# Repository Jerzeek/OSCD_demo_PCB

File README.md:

# OSCD Demo PCB

A demonstration / teaching PCB built by the [Open Science Community Delft](https://www.tudelft.nl/en/library/open-science-community-delft) to show what an open hardware project looks like in practice: full sources, an open licence, and everything needed to have the board made and reprogrammed by anyone.

It is a round, ~93 mm ESP32-C3 board shaped like the OSCD logo, with a ring of 12 addressable RGB LEDs, three sensors on a shared I²C bus, capacitive touch pads, and three push buttons. Plug it into USB-C, and the demo firmware lights the ring in response to tilt, touch, ambient light, and button presses.

| | |
|---|---|
| **Revision** | 1.0 |
| **Designer** | Dr. ir. Tim M. J. Nijssen, Open Science Community Delft |
| **Licence** | [CERN-OHL-P v2](LICENSE) (permissive) |
| **EDA tool** | KiCad (2026-era release — see [Opening the design](#opening-the-design)) |

---

## Features

| Block | Part | Interface |
|---|---|---|
| Microcontroller | ESP32-C3-MINI-1 (RISC-V, Wi-Fi + BLE, native USB) | — |
| RGB LEDs | 12 × WS2812B-2020, in a 63 mm ring | 1-wire, `GPIO8` |
| IMU | LSM6DS3 — 3-axis accelerometer + gyroscope | I²C `0x6A` |
| Ambient light | APDS-9306-065 | I²C `0x52` |
| Capacitive touch | MPR121 — 12 electrodes (6 buttons + 6-pad slider) | I²C `0x5A`, IRQ on `GPIO10` |
| Buttons | 3 × user push button, plus RESET and BOOT | `GPIO0/1/2` |
| Power | USB-C 5 V → HT7533-1 LDO → 3.3 V | — |
| Breakout | 2 × 2×5 pin header (5 V, 3.3 V, GND, 9 GPIO) | 2.54 mm |
| Test points | 5 V, 3.3 V, SDA, SCL (each via 100 Ω) | — |

There is no USB-UART bridge — the ESP32-C3's native USB peripheral is wired straight to the USB-C connector, protected by a USBLC6-2SC6 ESD array.

## Quick start

1. **Power it.** Connect a USB-C cable to `J1`. The board is bus-powered; no battery or jumper setting is needed.
2. **Install the toolchain.** Arduino IDE with the *esp32* board package by Espressif, board **ESP32C3 Dev Module**, and **Tools → USB CDC On Boot: Enabled**.
3. **Flash the demo.** Open [`firmware_examples/test_sensors/test_sensors.ino`](firmware_examples/test_sensors/test_sensors.ino) and upload it. Because there is no auto-reset circuit you must enter the bootloader by hand: **hold BOOT (SW2), tap RESET (SW1), release BOOT**, then click Upload. Tap RESET again when the upload finishes.
4. **Watch it.** The ring plays a rainbow sweep at boot, then reacts to tilt, touch, and the three buttons. Open the Serial Monitor at 115200 baud for sensor readings.

Full setup notes, required libraries, and troubleshooting are in [`firmware_examples/README.md`](firmware_examples/README.md).

## Pinout

| ESP32-C3 pin | Function on this board | Also on |
|---|---|---|
| `GPIO0` | Button **SW4** (active low, RC-debounced) | `J2.6` |
| `GPIO1` | Button **SW3** (active low, RC-debounced) | `J2.7` |
| `GPIO2` | Button **SW5** (active low, RC-debounced) | `J2.3` |
| `GPIO3` | APDS-9306 interrupt | `J2.4` |
| `GPIO4` | LSM6DS3 `INT1` | `J2.9` |
| `GPIO5` | LSM6DS3 `INT2` | `J3.3` |
| `GPIO6` | **I²C SCL** (4.7 kΩ pull-up) | `J3.4`, `TP5` |
| `GPIO7` | **I²C SDA** (4.7 kΩ pull-up) | `J3.5`, `TP6` |
| `GPIO8` | WS2812B data out → `D1` | `J3.6` |
| `GPIO9` | BOOT button **SW2** (strapping pin) | `J3.7` |
| `GPIO10` | MPR121 `IRQ` | `J2.8` |
| `GPIO18/19` | USB D− / D+ | — |
| `GPIO20/21` | UART0 RX / TX | `J3.8`, `J3.9` |
| `EN` | RESET button **SW1** | `J2.5` |

**Header pinouts** (2×5, 2.54 mm, odd/even numbering):

```
J2:  1 +5V    2 +3V3    3 GPIO2   4 GPIO3   5 EN
     6 GPIO0  7 GPIO1   8 GPIO10  9 GPIO4  10 GND

J3:  1 +5V    2 +3V3    3 GPIO5   4 GPIO6   5 GPIO7
     6 GPIO8  7 GPIO9   8 GPIO20  9 GPIO21 10 GND
```

**LED ring order:** `D1` sits at the 9 o'clock position and the chain `D1 → D2 → … → D12` runs clockwise, 30° apart.

**Touch electrodes:** `TP2` is the inner 6-pad slider on `ELE0…ELE5`; `TP1` is the outer ring of 6 buttons on `ELE6…ELE11`.

## Repository layout

```
OSCD_demo_PCB.kicad_pro     KiCad project
OSCD_demo_PCB.kicad_sch     Schematic (single sheet)
OSCD_demo_PCB.kicad_pcb     Board layout (4 layers)
schematic.pdf               Rendered schematic, for reading without KiCad
assets/
  OSCD_demo_PCB_symbols.kicad_sym    Project-local symbols
  OSCD_demo_PCB_footprints.pretty/   Project-local footprints (ESP32 module,
                                     touch pads, WS2812B-2020, logo, switches)
  graphics/                          OSCD logo artwork (DXF)
bom/ibom.html               Interactive HTML BOM for hand assembly
production/                 Fabrication outputs (gerbers, drill, BOM, CPL)
firmware_examples/          Arduino sketches
docs/                       Hardware and manufacturing documentation
```

## Opening the design

The sources were saved by a 2026-era KiCad release (schematic file format `20260306`, board format `20260206`). Open them with that release or newer; older KiCad versions will refuse the files.

Symbol and footprint libraries are project-local and resolved through `${KIPRJMOD}` in `sym-lib-table` / `fp-lib-table`, so cloning the repository and opening `OSCD_demo_PCB.kicad_pro` is enough — nothing has to be installed into your global libraries.

## Documentation

- **[docs/hardware.md](docs/hardware.md)** — how each subsystem works, jumper/configuration options, and design notes.
- **[docs/manufacturing.md](docs/manufacturing.md)** — board specification, ordering, and how to regenerate the fabrication files.
- **[firmware_examples/README.md](firmware_examples/README.md)** — toolchain setup, upload procedure, and what the demo does.

## Licence

Hardware and firmware are released under the **CERN Open Hardware Licence Version 2 – Permissive** ([`LICENSE`](LICENSE)). You may use, study, modify, manufacture and sell boards based on this design, including in closed-source products, provided you keep the copyright and licence notices and do not imply endorsement.

The OSCD logo and name are project branding; please replace them with your own if you distribute modified boards.

## Credits

Designed by Dr. ir. Tim M. J. Nijssen for the Open Science Community Delft.

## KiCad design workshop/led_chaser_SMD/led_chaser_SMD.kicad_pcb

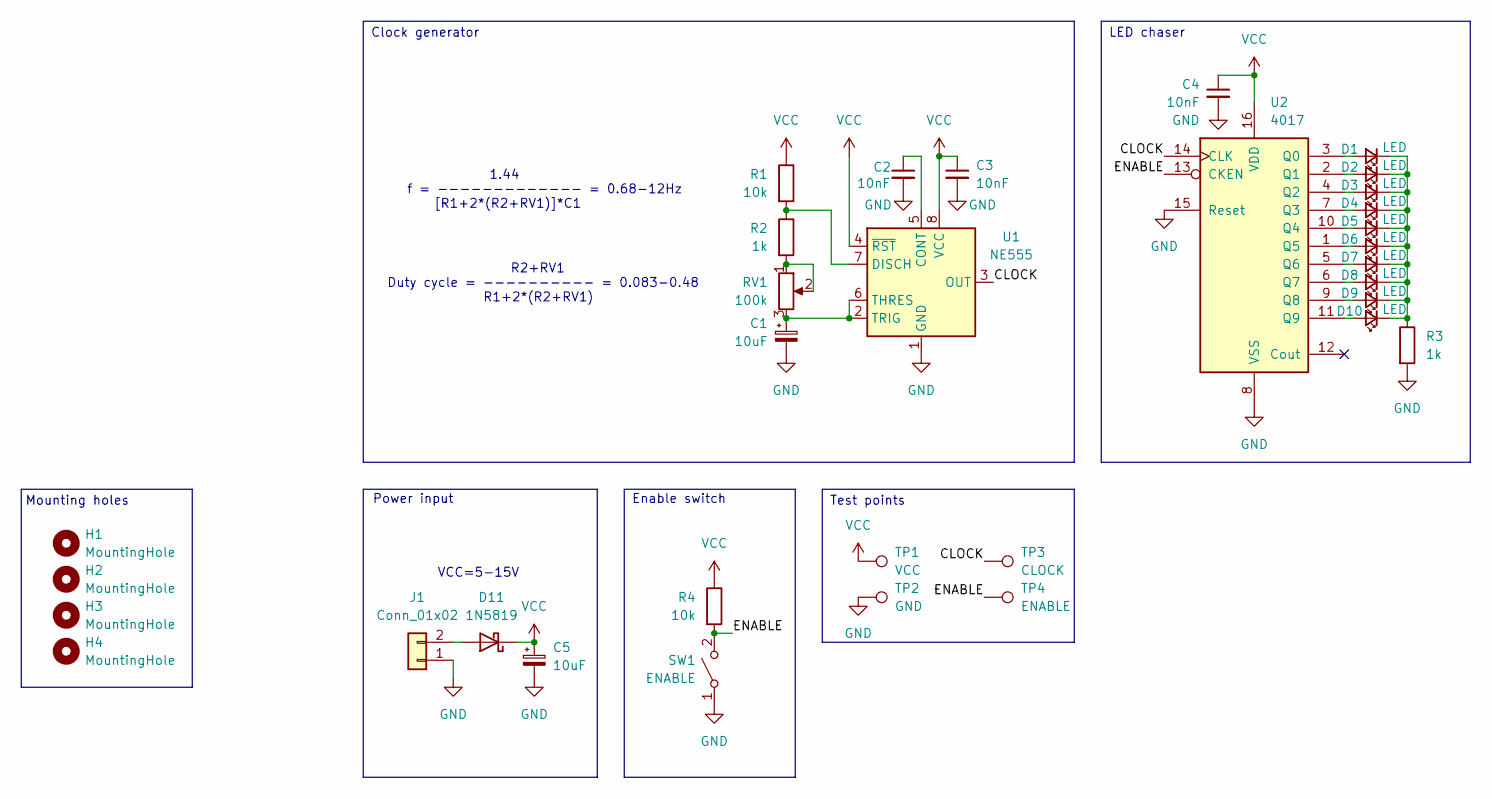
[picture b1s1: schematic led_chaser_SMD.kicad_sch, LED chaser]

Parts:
C1, C5: 10uF; C_0805_2012Metric_Pad1.18x1.45mm_HandSolder
C2, C3, C4: 10nF; C_0805_2012Metric_Pad1.18x1.45mm_HandSolder
D1, D2, D3, D4, D5, D6, D7, D8, D9, D10: LED; LED_0805_2012Metric_Pad1.15x1.40mm_HandSolder
D11: 1N5819; D_SOD-323
H1, H2, H3, H4: MountingHole; MountingHole_3.2mm_M3
J1: Conn_01x02; JST_XH_B2B-XH-A_1x02_P2.50mm_Vertical
R1, R4: 10k; R_0805_2012Metric_Pad1.20x1.40mm_HandSolder
R2, R3: 1k; R_0805_2012Metric_Pad1.20x1.40mm_HandSolder
RV1: 100k; Potentiometer_Bourns_TC33X_Vertical
SW1: ENABLE; SW_DIP_SPSTx01_Slide_6.7x4.1mm_W8.61mm_P2.54mm_LowProfile
TP1: VCC; TestPoint_Pad_D2.0mm
TP2: GND; TestPoint_Pad_D2.0mm
TP3: CLOCK; TestPoint_Pad_D2.0mm
TP4: ENABLE; TestPoint_Pad_D2.0mm
U1: NE555; SOIC-8_3.9x4.9mm_P1.27mm
U2: 4017; SOIC-16_3.9x9.9mm_P1.27mm

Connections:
/CLOCK: TP3.1 (1_1), U1.3 (OUT), U2.14 (CLK)
/ENABLE: R4.2, SW1.2 (B), TP4.1 (1_1), U2.13 (CKEN)
GND: C1.2, C2.2, C3.2, C4.2, C5.2, J1.1, R3.2, SW1.1 (A), TP2.1 (1_1), U1.1 (GND), U2.8 (VSS), U2.15 (Reset)
unnamed: D1.2 (A), U2.3 (Q0)
unnamed: D1.1 (K), D2.1 (K), D3.1 (K), D4.1 (K), D5.1 (K), D6.1 (K), D7.1 (K), D8.1 (K), D9.1 (K), D10.1 (K), R3.1
unnamed: D2.2 (A), U2.2 (Q1)
unnamed: D3.2 (A), U2.4 (Q2)
unnamed: D4.2 (A), U2.7 (Q3)
unnamed: D5.2 (A), U2.10 (Q4)
unnamed: D6.2 (A), U2.1 (Q5)
unnamed: D7.2 (A), U2.5 (Q6)
unnamed: D8.2 (A), U2.6 (Q7)
unnamed: D9.2 (A), U2.9 (Q8)
unnamed: D10.2 (A), U2.11 (Q9)
unnamed: D11.2 (A), J1.2
unnamed: R2.2, RV1.1, RV1.2
unnamed: C2.1, U1.5 (CONT)
unnamed: R1.2, R2.1, U1.7 (DISCH)
unnamed: C1.1, RV1.3, U1.2 (TRIG), U1.6 (THRES)
VCC: C3.1, C4.1, C5.1, D11.1 (K), R1.1, R4.1, TP1.1 (1_1), U1.4 (~RST), U1.8 (VCC), U2.16 (VDD)

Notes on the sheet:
Enable switch
LED chaser
R2+RV1 Duty cycle = ---------- = 0.083-0.48 R1+2*(R2+RV1)
1.44 f = ------------- = 0.68-12Hz [R1+2*(R2+RV1)]*C1
Test points
Clock generator
Mounting holes
Power input
VCC=5-15V

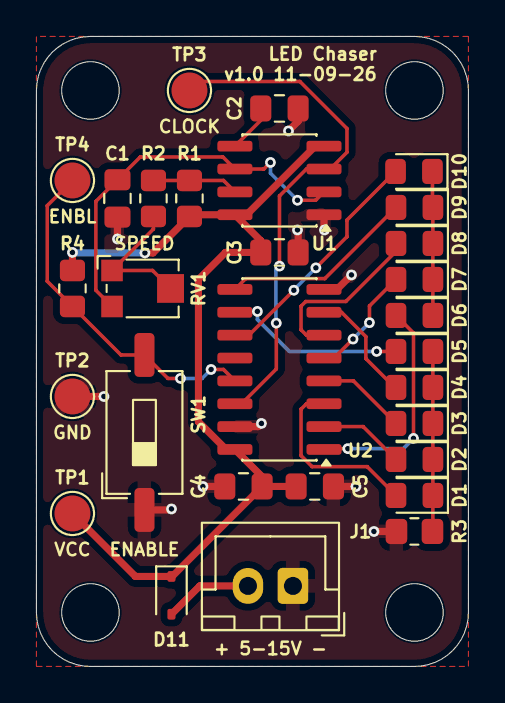
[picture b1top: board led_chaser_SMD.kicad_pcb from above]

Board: 2 copper layers, 24.0 x 35.0 mm, 33 parts (0 on the bottom side), 20 nets.

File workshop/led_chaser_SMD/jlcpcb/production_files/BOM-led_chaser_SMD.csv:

Comment,Designator,Footprint,LCSC,Quantity
100k,RV1,Potentiometer_Bourns_TC33X_Vertical,C48997895,1
10k,"R1,R4",R_0805_2012Metric_Pad1.20x1.40mm_HandSolder,C17414,2
10nF,"C2,C3,C4",C_0805_2012Metric_Pad1.18x1.45mm_HandSolder,C1710,3
10uF,"C1,C5",C_0805_2012Metric_Pad1.18x1.45mm_HandSolder,C15850,2
1N5819,D11,D_SOD-323,C191023,1
1k,"R2,R3",R_0805_2012Metric_Pad1.20x1.40mm_HandSolder,C17513,2
4017,U2,SOIC-16_3.9x9.9mm_P1.27mm,C2868374,1
ENABLE,SW1,SW_DIP_SPSTx01_Slide_6.7x4.1mm_W8.61mm_P2.54mm_LowProfile,C600988,1
LED,"D1,D10,D2,D3,D4,D5,D6,D7,D8,D9",LED_0805_2012Metric_Pad1.15x1.40mm_HandSolder,C84256,10
NE555,U1,SOIC-8_3.9x4.9mm_P1.27mm,C7593,1

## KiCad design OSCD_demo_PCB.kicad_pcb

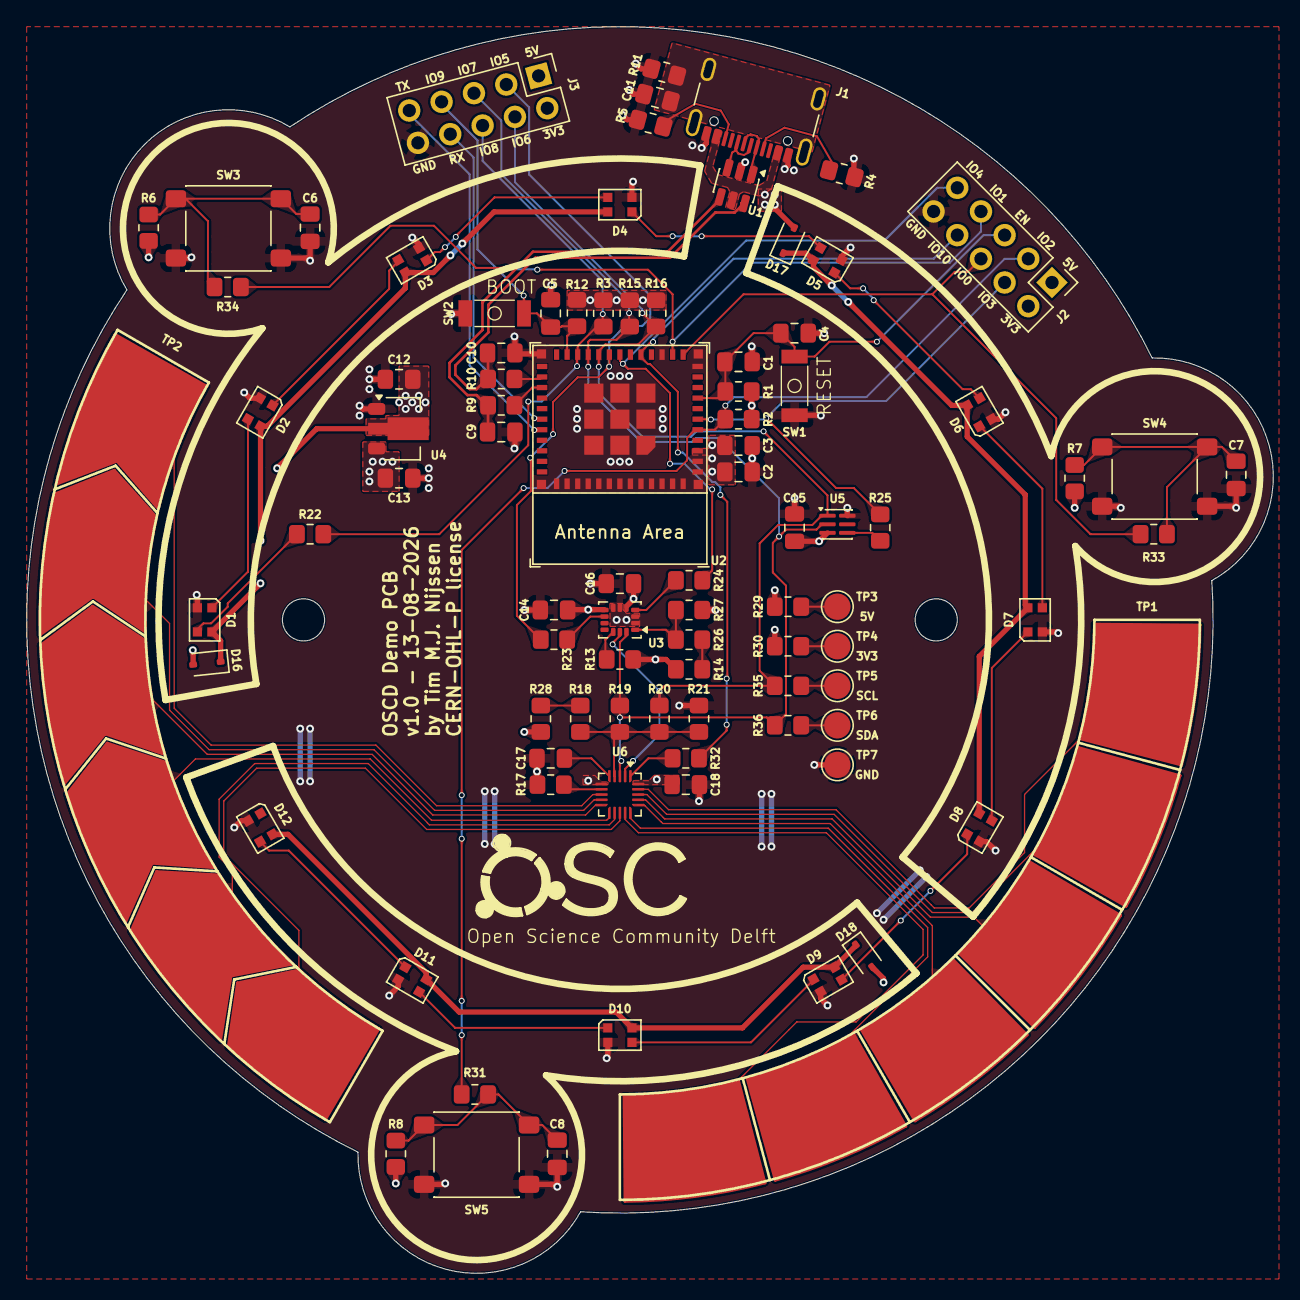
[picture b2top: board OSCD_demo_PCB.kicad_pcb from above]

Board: 4 copper layers, 94.6 x 94.6 mm, 90 parts (0 on the bottom side), 71 nets.

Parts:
C1: 1u; C_0805_2012Metric_Pad1.18x1.45mm_HandSolder
C2, C12, C13, C14, C15, C16: 10u; C_0805_2012Metric_Pad1.18x1.45mm_HandSolder
C3, C4, C5, C6, C7, C8, C17, C18: 100n; C_0805_2012Metric_Pad1.18x1.45mm_HandSolder
C9, C10: 22p; C_0805_2012Metric_Pad1.18x1.45mm_HandSolder
C11: 4.7n/1kV; C_0805_2012Metric_Pad1.18x1.45mm_HandSolder
D1, D2, D3, D4, D5, D6, D7, D8, D9, D10, D11, D12: WS2812B; LED_WS2812B-2020_PLCC4_2.0x2.0mm
D16, D17, D18: 1N5819WS; D_SOD-323
J1: USB_C_Receptacle_USB2.0_16P; USB_C_Receptacle_GCT_USB4105-xx-A_16P_TopMnt_Horizontal
J2, J3: Conn_01x12; PinHeader_2x05_P2.54mm_Vertical
R1, R2, R3, R6, R7, R8, R12, R13, R14, R28: 10k; R_0805_2012Metric_Pad1.20x1.40mm_HandSolder
R4, R5: 5k1; R_0805_2012Metric_Pad1.20x1.40mm_HandSolder
R9, R10, R18, R19, R20, R21, R22, R23, R24, R25, R26, R27, R31, R32, R33, R34: 0R; R_0805_2012Metric_Pad1.20x1.40mm_HandSolder
R11: 1M; R_0805_2012Metric_Pad1.20x1.40mm_HandSolder
R15, R16: 4k7; R_0805_2012Metric_Pad1.20x1.40mm_HandSolder
R17: 75k/1%; R_0805_2012Metric_Pad1.20x1.40mm_HandSolder
R29, R30, R35, R36: 100R; R_0805_2012Metric_Pad1.20x1.40mm_HandSolder
SW1: RESET; SMD_SW_1P1T_TS-1088-AR02016
SW2: BOOT; SMD_SW_1P1T_TS-1088-AR02016
SW3, SW4, SW5: PB; SW_SPST_PTS645Sx43SMTR92
TP1: 6_pad_touch_slider; 6_pad_touch_buttons
TP2: 6_pad_touch_slider
TP3: 5V; TestPoint_Pad_D2.0mm
TP4: 3V3; TestPoint_Pad_D2.0mm
TP5: SCL; TestPoint_Pad_D2.0mm
TP6: SDA; TestPoint_Pad_D2.0mm
TP7: GND; TestPoint_Pad_D2.0mm
U1: USBLC6-2SC6; SOT-23-6
U2: ESP32-C3-MINI-1
U3: LSM6DS3; LGA-14_3x2.5mm_P0.5mm_LayoutBorder3x4y
U4: HT7533-1-SOT89; SOT-89-3
U5: APDS-9306-065; Broadcom_DFN-6_2x2mm_P0.65mm
U6: MPR121QR2; UQFN-20_3x3mm_P0.4mm

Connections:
+3.3V: C2.1, C3.1, C13.1, C14.1, C15.1, C16.1, C18.2, J2.2, J3.2, R1.1, R2.2, R3.2, R6.2, R7.2, R8.2, R12.1, R13.1, R14.2, R15.2, R16.2, R28.2, R30.1, U2.3 (3V3), U3.5 (VDDIO), U3.8 (VDD), U4.3 (VOUT), U5.3 (VDD), U6.20 (VDD)
+5V: C12.1, D16.2 (A), D17.2 (A), D18.2 (A), J1.A4 (VBUS), J1.A9 (VBUS), J1.B4 (VBUS), J1.B9 (VBUS), J2.1, J3.1, R29.1, U1.5 (VBUS), U4.2 (VIN)
/EN/CHIP_PU: C1.1, C4.1, J2.5, R1.2, SW1.2, U2.8 (EN/CHIP_PU)
/GPIO0/ADC: J2.6, R33.1, U2.12 (GPIO0/ADC1_CH0/XTAL_32K_P)
/GPIO1/ADC: J2.7, R34.1, U2.13 (GPIO1/ADC1_CH1/XTAL_32K_N)
/GPIO2/ADC: J2.3, R2.1, R31.1, U2.5 (GPIO2/ADC1_CH2)
/GPIO3/ADC: J2.4, R25.1, U2.6 (GPIO3/ADC1_CH3)
/GPIO4/ADC: J2.9, R24.1, U2.18 (GPIO4/ADC1_CH4)
/GPIO5/ADC: J3.3, R23.1, U2.19 (GPIO5/ADC2_CH0)
/GPIO6/SCL: J3.4, R16.1, R20.2, R35.1, U2.20 (GPIO6), U3.13 (SCL), U5.1 (SCL), U6.2 (SCL)
/GPIO7/SDA: J3.5, R15.1, R19.2, R36.1, U2.21 (GPIO7), U3.14 (SDA), U5.2 (SDA), U6.3 (SDA)
/GPIO8: J3.6, R3.1, R22.1, U2.22 (GPIO8)
/GPIO9/BOOT: C5.2, J3.7, R12.2, SW2.1, U2.23 (GPIO9)
/GPIO10: J2.8, R32.2, U2.16 (GPIO10)
/GPIO20/RX: J3.8, U2.30 (GPIO20/U0RXD)
/GPIO21/TX: J3.9, U2.31 (GPIO21/U0TXD)
/USB_D+: C9.2, R9.2, U1.4 (I/O2)
/USB_D-: C10.2, R10.2, U1.6 (I/O1)
GND: C1.2, C2.2, C3.2, C4.2, C5.1, C6.1, C7.1, C8.1, C9.1, C10.1, C11.1, C12.2, C13.2, C14.2, C15.2, C16.2, C17.1, C18.1, D1.2 (VSS), D2.2 (VSS), D3.2 (VSS), D4.2 (VSS), D5.2 (VSS), D6.2 (VSS), D7.2 (VSS), D8.2 (VSS), D9.2 (VSS), D10.2 (VSS), D11.2 (VSS), D12.2 (VSS), J1.A1 (GND), J1.A12 (GND), J1.B1 (GND), J1.B12 (GND), J2.10, J3.10, R4.2, R5.2, R11.1, R17.1, R21.2, R27.2, SW1.1, SW2.2, SW3.2, SW4.2, SW5.2, TP7.1 (1_1), U1.2 (GND), U2.1 (GND), U2.2 (GND), U2.11 (GND), U2.14 (GND), U2.36 (GND), U2.37 (GND), U2.38 (GND), U2.39 (GND), U2.40 (GND), U2.41 (GND), U2.42 (GND), U2.43 (GND), U2.44 (GND), U2.45 (GND), U2.46 (GND), U2.47 (GND), U2.48 (GND), U2.49 (GND), U2.50 (GND), U2.51 (GND), U2.52 (GND), U2.53 (GND), U3.2 (SDX), U3.3 (SCX), U3.6 (GND), U3.7 (GND), U4.1 (GND), U5.6 (GND), U6.6 (VSS)
unnamed: C6.2, R6.1, R34.2, SW3.1
unnamed: C7.2, R7.1, R33.2, SW4.1
unnamed: C8.2, R8.1, R31.2, SW5.1
unnamed: D1.3 (DIN), R22.2
unnamed: D1.1 (DOUT), D2.3 (DIN)
unnamed: D1.4 (VDD), D2.4 (VDD), D3.4 (VDD), D4.4 (VDD), D16.1 (K)
unnamed: D2.1 (DOUT), D3.3 (DIN)
unnamed: D3.1 (DOUT), D4.3 (DIN)
unnamed: D4.1 (DOUT), D5.3 (DIN)
unnamed: D5.1 (DOUT), D6.3 (DIN)
unnamed: D6.1 (DOUT), D7.3 (DIN)
unnamed: D7.1 (DOUT), D8.3 (DIN)
unnamed: D8.1 (DOUT), D9.3 (DIN)
unnamed: D9.1 (DOUT), D10.3 (DIN)
unnamed: D10.1 (DOUT), D11.3 (DIN)
unnamed: D9.4 (VDD), D10.4 (VDD), D11.4 (VDD), D12.4 (VDD), D18.1 (K)
unnamed: D11.1 (DOUT), D12.3 (DIN)
unnamed: D5.4 (VDD), D6.4 (VDD), D7.4 (VDD), D8.4 (VDD), D17.1 (K)
unnamed: J1.A5 (CC1), R4.1
unnamed: J1.B5 (CC2), R5.1
unnamed: J1.A6 (D+), J1.B6 (D+), U1.3 (I/O2)
unnamed: J1.A7 (D-), J1.B7 (D-), U1.1 (I/O1)
unnamed: C11.2, J1.SH (SHIELD), R11.2
unnamed: R14.1, R26.2
unnamed: R18.2, R28.1
unnamed: R29.2, TP3.1 (1_1)
unnamed: R30.2, TP4.1 (1_1)
unnamed: R35.2, TP5.1 (1_1)
unnamed: R36.2, TP6.1 (1_1)
unnamed: R10.1, U2.26 (GPIO18/USB_D-)
unnamed: R9.1, U2.27 (GPIO19/USB_D+)
unnamed: R13.2, U3.12 (CS)
unnamed: R24.2, U3.4 (INT1)
unnamed: R23.2, U3.9 (INT2)
unnamed: R26.1, R27.1, U3.1 (SDO/SA0)
unnamed: R25.2, U5.4 (INT)
unnamed: R18.1, R19.1, R20.1, R21.1, U6.4 (ADDR)
unnamed: TP2.6 (Pad_6), U6.8 (ELE0)
unnamed: TP2.5 (Pad_5), U6.9 (ELE1)
unnamed: TP2.4 (Pad_4), U6.10 (ELE2)
unnamed: TP2.3 (Pad_3), U6.11 (ELE3)
unnamed: TP2.2 (Pad_2), U6.12 (LED0/ELE4)
unnamed: TP2.1 (Pad_1), U6.13 (LED1/ELE5)
unnamed: TP1.6 (Pad_6), U6.14 (LED2/ELE6)
unnamed: TP1.5 (Pad_5), U6.15 (LED3/ELE7)
unnamed: TP1.4 (Pad_4), U6.16 (LED4/ELE8)
unnamed: TP1.3 (Pad_3), U6.17 (LED5/ELE9)
unnamed: TP1.2 (Pad_2), U6.18 (LED6/ELE10)
unnamed: TP1.1 (Pad_1), U6.19 (LED7/ELE11)
unnamed: R17.2, U6.7 (REXT)
unnamed: C17.2, U6.5 (VREG)
unnamed: R32.1, U6.1 (~IRQ)

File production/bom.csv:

Designator,Footprint,Quantity,Value,LCSC Part #
C1,0805,1,1u,C28323
C11,0805,1,4.7n/1kV,C565695
"C12, C13, C14, C15, C16, C2",0805,6,10u,C15850
"C17, C18, C3, C4, C5, C6, C7, C8",0805,8,100n,C49678
"D1, D10, D11, D12, D2, D3, D4, D5, D6, D7, D8, D9",LED_WS2812B-2020_PLCC4_2.0x2.0mm,12,WS2812B,C2976072
"D16, D17, D18",D_SOD-323,3,1N5819WS,C191023
J1,USB_C_Receptacle_GCT_USB4105-xx-A_16P_TopMnt_Horizontal,1,USB_C_Receptacle_USB2.0_16P,C393939
"J2, J3",PinHeader_2x05_P2.54mm_Vertical,2,Conn_01x12,
"R1, R12, R13, R14, R2, R28, R3, R6, R7",0805,9,10k,C17414
"R10, R21, R22, R23, R24, R25, R27, R31, R32, R33, R34, R9",0805,12,0R,C17477
R11,0805,1,1M,C17514
"R15, R16",0805,2,4k7,C17673
R17,0805,1,75k/1%,C17819
"R29, R30, R35, R36",0805,4,100R,C17408
"R4, R5",0805,2,5k1,C27834
SW1,SMD_SW_1P1T_TS-1088-AR02016,1,RESET,C720477
SW2,SMD_SW_1P1T_TS-1088-AR02016,1,BOOT,C720477
"SW3, SW4, SW5",SW_SPST_PTS645Sx43SMTR92,3,PB,C2837531
U1,SOT-23-6,1,USBLC6-2SC6,C7519
U2,ESP32-C3-MINI-1,1,ESP32-C3-MINI-1,C2838502
U3,LGA-14_3x2.5mm_P0.5mm_LayoutBorder3x4y,1,LSM6DS3,C967633
U4,SOT-89-3,1,HT7533-1-SOT89,C14289
U5,Broadcom_DFN-6_2x2mm_P0.65mm,1,APDS-9306-065,C2649498
U6,UQFN-20_3x3mm_P0.4mm,1,MPR121QR2,C91322

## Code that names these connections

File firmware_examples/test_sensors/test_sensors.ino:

/*  OSCD Demo PCB — Firmware demo
 *  Open Science Community Delft
 *  
 *  v1.0, 07-09-2026, Dr.ir. Tim M.J. Nijssen
 *  CERN-OHL-P license
 *
 *  Tests all sensors on the board to see that each subsystem works:
 *   - 12x WS2812B RGB LEDs
 *   - LSM6DS3 accelerometer/gyroscope (I2C)
 *   - APDS-9306-065 ambient light sensor (I2C, direct register access)
 *   - MPR121 12-channel capacitive touch controller (I2C)
 *   - 3x push buttons
 *
 *  ---------------------------------------------------------------------
 *  ARDUINO IDE SETUP
 *  ---------------------------------------------------------------------
 *  1. Board package: "esp32" by Espressif Systems (Boards Manager)
 *  2. Board: "ESP32C3 Dev Module"
 *  3. Tools -> USB CDC On Boot: "Enabled"   <-- required, or Serial won't
 *     appear over the native USB port
 *  4. This board has no USB-UART bridge, so there is no auto-reset circuit.
 *     To upload: hold BOOT (SW2), tap RESET (SW1), release BOOT, THEN
 *     click Upload. Ensure all serial monitors are closed before uploading.
 *  5. After uploading is completed, tap RESET (SW1)
 *
 *  LIBRARIES (all installable via Library Manager)
 *   - "Adafruit NeoPixel"            (WS2812B)
 *   - "Adafruit LSM6DS"              (IMU — pulls in Adafruit_LSM6DS3TRC)
 *   - "Adafruit Unified Sensor"      (dependency of the above)
 *   - "Adafruit MPR121"              (capacitive touch)
 *  (The APDS-9306-065 light sensor has no common Arduino library, so it's
 *   talked to directly over Wire — this also doubles as a simple example
 *   of raw I2C register access.)
 *
 *  ---------------------------------------------------------------------
 *  BOARD PINOUT (OSCD Demo PCB Rev 1.0)
 *  ---------------------------------------------------------------------
 *  I2C SDA          GPIO7   (LSM6DS3 @0x6A, APDS-9306-065 @0x52, MPR121 @0x5A)
 *  I2C SCL          GPIO6
 *  WS2812 data      GPIO8   (12 LEDs)
 *  Button SW3       GPIO1   (active low)
 *  Button SW4       GPIO0   (active low)
 *  Button SW5       GPIO2   (active low)
 *  MPR121 IRQ       GPIO10  (not used here)
 *  LSM6DS3 INT1     GPIO4   (not used here)
 *  LSM6DS3 INT2     GPIO5   (not used here)
 */

#include <Wire.h>
#include <Adafruit_NeoPixel.h>
#include <Adafruit_LSM6DS3TRC.h>
#include <Adafruit_MPR121.h>

// ---------- Pin definitions ----------
#define PIN_SDA 7
#define PIN_SCL 6

#define PIN_LED_DATA 8
#define NUM_LEDS 12

#define NUM_BTNS 3
#define PIN_BTN_SW3 1
#define PIN_BTN_SW4 0
#define PIN_BTN_SW5 2

#define NUM_TOUCH 12

#define MPR121_ADDR 0x5A
#define LSM6DS3_ADDR 0x6A
#define APDS9306_ADDR 0x52

// --- APDS-9306-065 helper functions ---
#include <APDS9306.h>

// ---------- Objects ----------
Adafruit_NeoPixel strip(NUM_LEDS, PIN_LED_DATA, NEO_GRB + NEO_KHZ800);
Adafruit_LSM6DS3TRC imu;
Adafruit_MPR121 touch = Adafruit_MPR121();

bool imuOk = false;
bool touchOk = false;
bool alsOk = false;

uint32_t lastSensorPrint = 0;

// ======================================================================
//  Setup
// ======================================================================
void setup() {
  // --- Serial ---
  Serial.begin(115200);
  Serial.setTxTimeoutMs(0); // prevent USB CDC port from blocking the sketch
  uint32_t t0 = millis();
  while (!Serial && millis() - t0 < 3000) {
    delay(10);
  }  // give USB CDC time to enumerate

  // --- buttons ---
  pinMode(PIN_BTN_SW3, INPUT);  // buttons have external pull-up resistors
  pinMode(PIN_BTN_SW4, INPUT);
  pinMode(PIN_BTN_SW5, INPUT);

  // --- led strip ---
  strip.begin();
  strip.setBrightness(60);
  strip.show();  // all off

  // --- I2C ---
  Wire.begin(PIN_SDA, PIN_SCL);
  Wire.setClock(400000);
  delay(100);

  // --- IMU ---
  if (imu.begin_I2C(LSM6DS3_ADDR, &Wire)) {
    imuOk = true;
  }

  // --- Ambient light sensor ---
  alsOk = apds9306Init();
  Serial.println(alsOk ? "[OK]   APDS-9306-065 light sensor responding"
                       : "[FAIL] APDS-9306-065 light sensor not responding");

  // --- Capacitive touch ---
  if (touch.begin(MPR121_ADDR, &Wire)) {
    touchOk = true;
    touch.setAutoconfig(true);
  }

  // --- startup animation ---
  for (uint16_t i = 0; i < 2 * NUM_LEDS; i++) {
    strip.rainbow(i * 0x10000 / NUM_LEDS, 1, 255, 255, true);
    strip.show();
    delay(100);
  }
  strip.clear();
  strip.show();
}

// ======================================================================
//  Main loop
// ======================================================================
void loop() {
  handleButtons();

  if (alsOk)
    handleAls();

  if (imuOk)
    handleImu();

  if (touchOk)
    handleTouch();

  if (Serial && millis() - lastSensorPrint > 500) {
    lastSensorPrint = millis();
    printSensorReadings();
  }
}

// ---------- Buttons -> LED flashes  ----------
void handleButtons() {
  static bool lastState[NUM_BTNS] = { true, true, true };  // pulled up = true when idle
  int pins[NUM_BTNS] = { PIN_BTN_SW3, PIN_BTN_SW4, PIN_BTN_SW5 };

  for (uint8_t i = 0; i < NUM_BTNS; i++) {
    bool state = digitalRead(pins[i]);
    if (state != lastState[i]) {
      uint8_t first_led = i * NUM_LEDS / NUM_BTNS;       // first led of the segment
      uint8_t last_led = (i + 1) * NUM_LEDS / NUM_BTNS;  // first led of the next segment
      uint16_t hue = i * 0x10000 / NUM_BTNS;

      if (!state) {  // pressed
        for (uint8_t j = first_led; j < last_led; j++) {
          strip.setPixelColor(j, strip.gamma32(strip.ColorHSV(hue, 255, 255)));
        }
      } else {  // released
        for (uint8_t j = first_led; j < last_led; j++) {
          strip.setPixelColor(j, 0);
        }
      }
      strip.show();
    }
    lastState[i] = state;
  }
}

// ---------- Ambient light -> LED brightness ----------
void handleAls() {
  const uint16_t max_lux = 10000;
  uint8_t brightness = map(constrain(apds9306ReadALS(), 0, max_lux), 0, max_lux, 0, 255);
  strip.setBrightness(brightness);
}

// ---------- Orientation -> LED mapping ----------
void handleImu() {
  static uint8_t lastLed = 0;
  const uint16_t hue = 0;

  float accel_x;
  float accel_y;
  float accel_z;

  imu.readAcceleration(accel_x, accel_y, accel_z);
  float angle = atan2(-accel_y, accel_x) + M_PI;
  float magsq = (accel_y*accel_y + accel_x*accel_x);
  
  uint8_t led = ((uint8_t) round(angle/(2*M_PI)*NUM_LEDS)) % NUM_LEDS;
  uint8_t val = (uint8_t) (magsq*255.);

  strip.setPixelColor(led, strip.ColorHSV(hue,255,val));

  if (led != lastLed) {
    strip.setPixelColor(lastLed, 0);
    strip.show();
    lastLed = led;
  }
}

// ---------- Capacitive touch -> LED mapping ----------
void handleTouch() {
  static uint16_t lastTouched = 0;
  const uint8_t led_map[NUM_TOUCH] = { 3, 2, 1, 0, 11, 10, 9, 8, 7, 6, 5, 4 };

  uint16_t currTouched = touch.touched();

  for (int i = 0; i < NUM_TOUCH; i++) {
    bool isTouched = currTouched & (1 << i);  // read bitmask
    bool wasTouched = lastTouched & (1 << i);

    if (isTouched) {                                                       // while pressed
      uint8_t val = (touch.baselineData(i) - touch.filteredData(i)) >> 2;  // touch sensor data, converted from 10 bit to 8 bit
      strip.setPixelColor(led_map[i], strip.ColorHSV(0, 0, val));
      strip.show();
    }

    if (!isTouched && wasTouched) {  // released
      uint8_t led = i % NUM_LEDS;
      strip.setPixelColor(led_map[i], 0);
      strip.show();
    }
  }
  lastTouched = currTouched;
}

// ---------- Periodic IMU / light sensor printout ----------
void printSensorReadings() {
  Serial.print("IMU    ");
  if (imuOk) {
    sensors_event_t accel;
    sensors_event_t gyro;
    sensors_event_t temp;
    imu.getEvent(&accel, &gyro, &temp);

    Serial.print("T[degC]=");
    Serial.print(temp.temperature);

    Serial.print("  accel[m/s^2] X=");
    Serial.print(accel.acceleration.x, 2);
    Serial.print(" Y=:");
    Serial.print(accel.acceleration.y, 2);
    Serial.print(" Z=");
    Serial.print(accel.acceleration.z, 2);

    /* Display the results (rotation is measured in rad/s) */
    Serial.print("  gyro[rad/s] X= ");
    Serial.print(gyro.gyro.x, 1);
    Serial.print(" Y=");
    Serial.print(gyro.gyro.y, 1);
    Serial.print(" Z=");
    Serial.print(gyro.gyro.z, 1);
  } else {
    Serial.print("not detected");
  }
  Serial.println();

  Serial.print("ALS    ");
  if (alsOk) {
    Serial.print("value[counts]=");
    Serial.print(apds9306ReadALS());
    Serial.println(" (roughly proportional to lux)");
  } else {
    Serial.println("not detected");
  }
  Serial.println();

  Serial.print("TOUCH  ");
  if (touchOk) {
    Serial.print("value[counts]");
    for (uint8_t i = 0; i < NUM_TOUCH; i++) {
      Serial.print("pad");
      Serial.print(i);
      Serial.print(" ");
      Serial.print(touch.baselineData(i) - touch.filteredData(i));
      Serial.print(" ");
    }
    Serial.println();
  } else {
    Serial.println("not detected");
  }
}
